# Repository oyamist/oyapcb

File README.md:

# oyapcb
OyaMist printed circuit boards

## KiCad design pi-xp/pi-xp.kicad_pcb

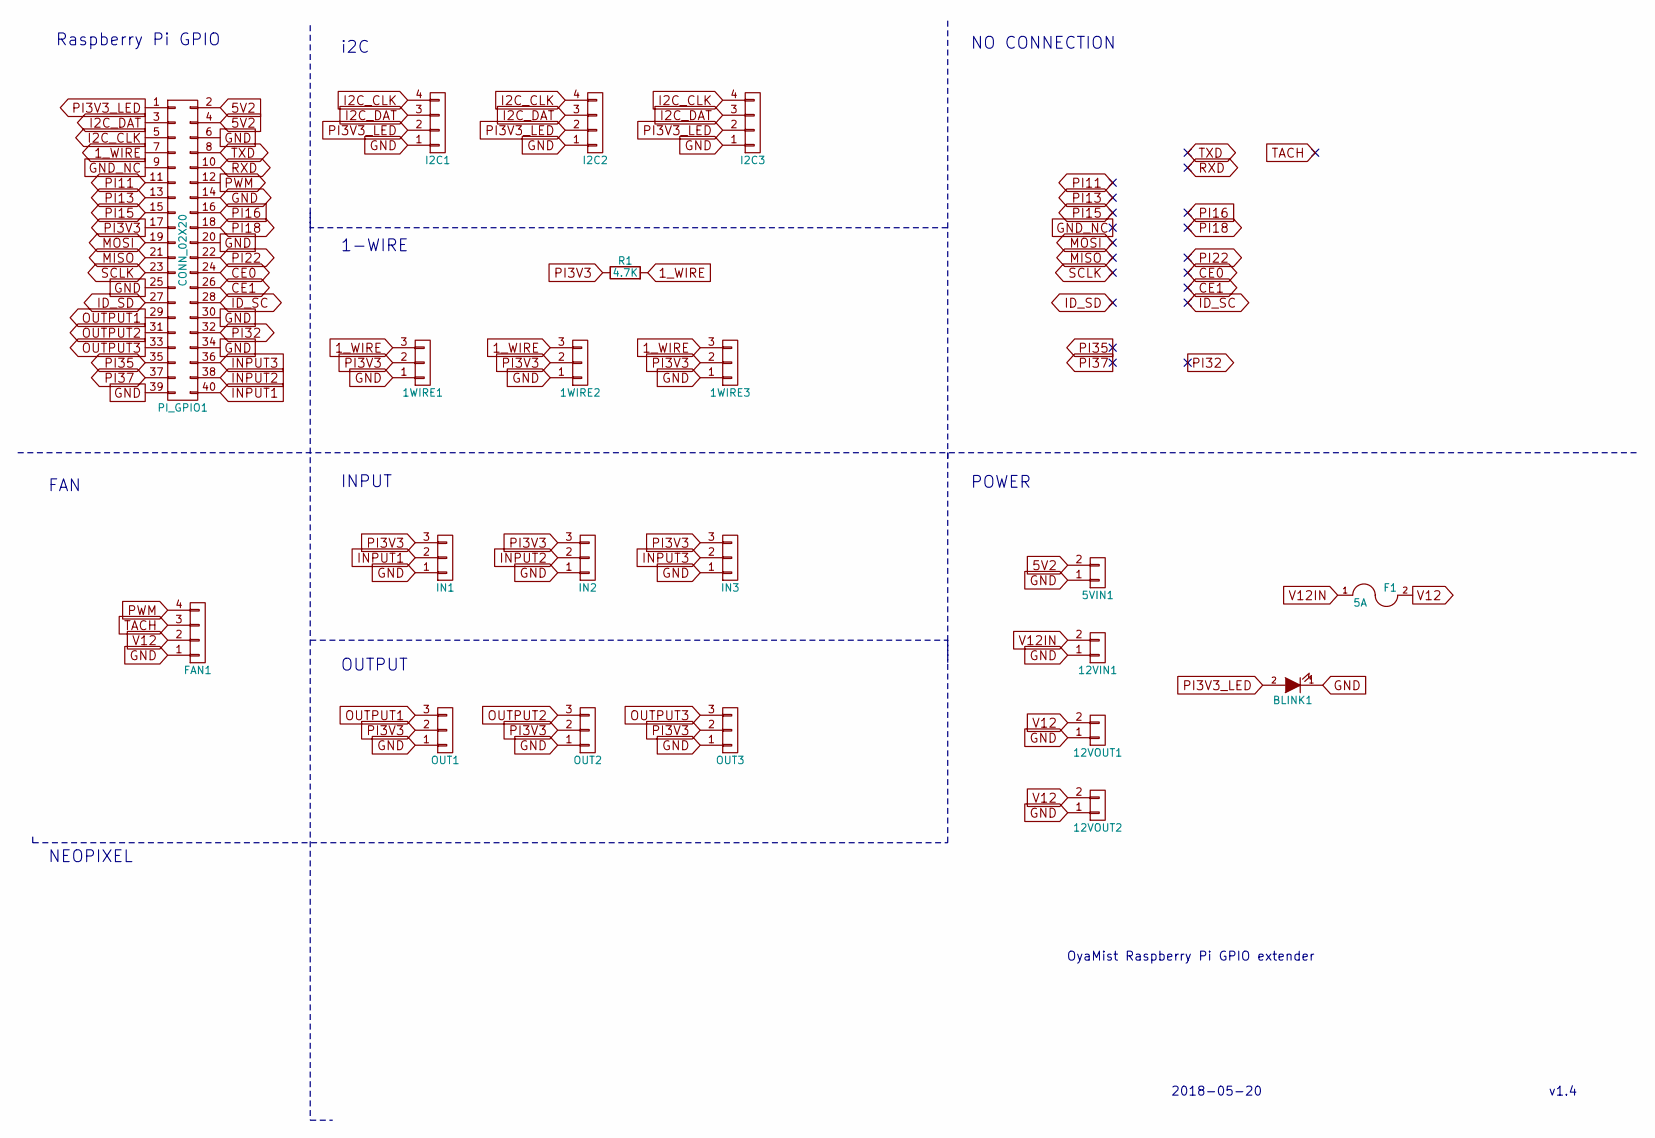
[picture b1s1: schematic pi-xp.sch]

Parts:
1WIRE1, 1WIRE2, 1WIRE3: CONN_01X03; Pin_Header_Straight_1x03_Pitch2.54mm
5VIN1: CONN_01X02; Pin_Header_Straight_1x02_Pitch2.54mm
12VIN1, 12VOUT1, 12VOUT2: CONN_01X02; TerminalBlock_bornier-2_P5.08mm
BLINK1: LED_BLNK; LED_D5.0mm
F1: 5A; Fuse_TE5_Littlefuse-395Series
FAN1: CONN_01X04; Fan_Pin_Header_Straight_1x04
I2C1, I2C2, I2C3: CONN_01X04; Pin_Header_Straight_1x04_Pitch2.54mm
IN1, IN2, IN3: CONN_01X03; Pin_Header_Straight_1x03_Pitch2.54mm
OUT1, OUT2, OUT3: CONN_01X03; Pin_Header_Straight_1x03_Pitch2.54mm
PI_GPIO1: CONN_02X20; Pin_Header_Straight_2x20_Pitch2.54mm
R1: 4.7K; R_Axial_DIN0207_L6.3mm_D2.5mm_P10.16mm_Horizontal

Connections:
1_WIRE: 1WIRE1.3, 1WIRE2.3, 1WIRE3.3, PI_GPIO1.7, R1.2
5V2: 5VIN1.2, PI_GPIO1.2, PI_GPIO1.4
CE0: PI_GPIO1.24
CE1: PI_GPIO1.26
GND: 1WIRE1.1, 1WIRE2.1, 1WIRE3.1, 5VIN1.1, 12VIN1.1, 12VOUT1.1, 12VOUT2.1, BLINK1.1 (K), FAN1.1, I2C1.1, I2C2.1, I2C3.1, IN1.1, IN2.1, IN3.1, OUT1.1, OUT2.1, OUT3.1, PI_GPIO1.6, PI_GPIO1.14, PI_GPIO1.20, PI_GPIO1.25, PI_GPIO1.30, PI_GPIO1.34, PI_GPIO1.39
GND_NC: PI_GPIO1.9
I2C_CLK: I2C1.4, I2C2.4, I2C3.4, PI_GPIO1.5
I2C_DAT: I2C1.3, I2C2.3, I2C3.3, PI_GPIO1.3
ID_SC: PI_GPIO1.28
ID_SD: PI_GPIO1.27
INPUT1: IN1.2, PI_GPIO1.40
INPUT2: IN2.2, PI_GPIO1.38
INPUT3: IN3.2, PI_GPIO1.36
MISO: PI_GPIO1.21
MOSI: PI_GPIO1.19
OUTPUT1: OUT1.3, PI_GPIO1.29
OUTPUT2: OUT2.3, PI_GPIO1.31
OUTPUT3: OUT3.3, PI_GPIO1.33
PI3V3: 1WIRE1.2, 1WIRE2.2, 1WIRE3.2, IN1.3, IN2.3, IN3.3, OUT1.2, OUT2.2, OUT3.2, PI_GPIO1.17, R1.1
PI3V3_LED: BLINK1.2 (A), I2C1.2, I2C2.2, I2C3.2, PI_GPIO1.1
PI11: PI_GPIO1.11
PI13: PI_GPIO1.13
PI15: PI_GPIO1.15
PI16: PI_GPIO1.16
PI18: PI_GPIO1.18
PI22: PI_GPIO1.22
PI32: PI_GPIO1.32
PI35: PI_GPIO1.35
PI37: PI_GPIO1.37
PWM: FAN1.4, PI_GPIO1.12
RXD: PI_GPIO1.10
SCLK: PI_GPIO1.23
TACH: FAN1.3
TXD: PI_GPIO1.8
V12: 12VOUT1.2, 12VOUT2.2, F1.2, FAN1.2
V12IN: 12VIN1.2, F1.1

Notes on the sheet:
Raspberry Pi GPIO
i2C
1-WIRE
OUTPUT
INPUT
POWER
FAN
NO CONNECTION
OyaMist Raspberry Pi GPIO extender
v1.4
2018-05-20
NEOPIXEL

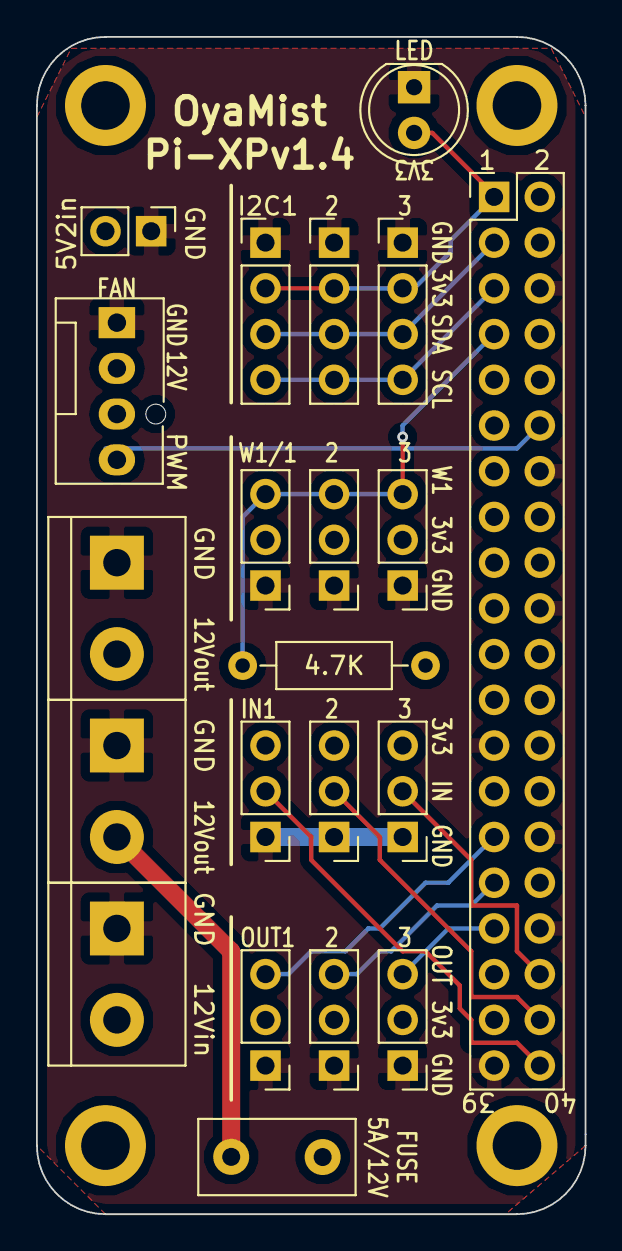
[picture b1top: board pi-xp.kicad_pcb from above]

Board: 2 copper layers, 30.5 x 65.4 mm, 21 parts (0 on the bottom side), 16 nets.

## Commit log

2018-04-18 pi-xp
2018-05-02 pi_xp v1.1
2018-05-13 PI_XP1.2
2018-05-20 v1.3
2018-05-21 ignore
2018-07-26 v1.4 I2C 3v3
2018-08-04 Dowel
